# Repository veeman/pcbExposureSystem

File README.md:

# pcbExposureSystem
Homepage [www.mage-dev.de](http://www.mage-dev.de/)   
Copyright (c) 2012 Vitalij Mast <mailto:vitalij-mast(at)mage-dev(dot).de>  
License see LICENSE file

# Description
This is a pcb exposure system project.
This repo contains the schamtic files and the source code for the uC ATmega88.

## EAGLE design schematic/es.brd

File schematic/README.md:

Eagle Schematic Files   
# WARNING
High Voltages can cause electric shock. Be extremely careful when working with high voltage!   
Work with High Voltages at your own risk!

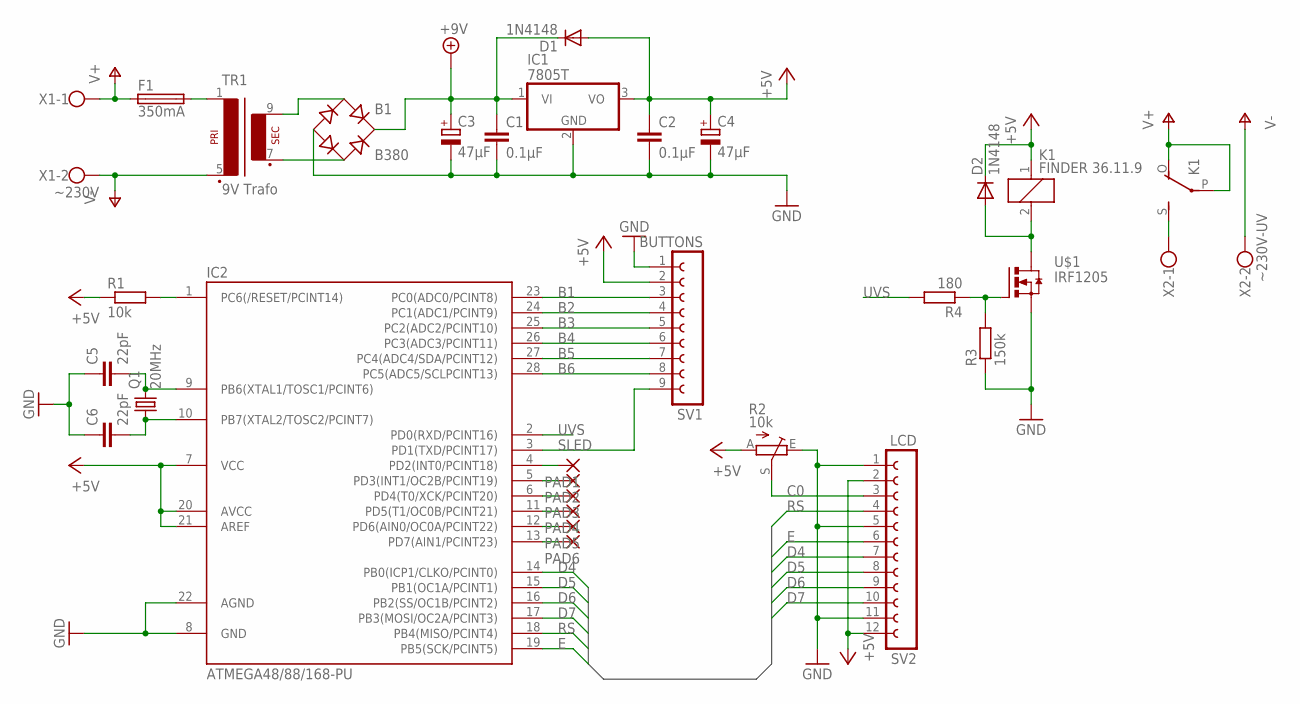
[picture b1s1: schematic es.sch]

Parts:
B1: B380; RB1A
C1, C2: 0.1µF; C025-024X044
C3, C4: 47µF; E2,5-5
C5, C6: 22pF; C050-024X044
D1, D2: 1N4148; DO35-7
F1: 350mA; SHK20Q
IC1: 7805T; TO220H
IC2: ATMEGA48/88/168-PU; DIL28-3
K1: FINDER 36.11.9; G5LE
PAD1, PAD2, PAD3, PAD4, PAD5, PAD6: 1,6/0,8
Q1: 20MHz; HC49/S
R1: 10k; 0204/7
R2: 10k; LI15
R3: 150k; 0204/7
R4: 180; 0204/7
SV1: BUTTONS; FE09
SV2: LCD; FE12
TR1: 9V Trafo; EI42-1
U$1: IRF1205; I-PAK_TO251AA
X1: ~230V; W237-2N
X2: ~230V-UV; W237-2N

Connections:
+5V: C2.1, C4.+, D1.A, D2.C, IC1.3 (VO), IC2.7 (VCC), IC2.20 (AVCC), IC2.21 (AREF), K1.1, R1.1, R2.A, SV1.2, SV2.2, SV2.12
+9V: B1.+, C1.1, C3.+, D1.C, IC1.1 (VI)
B1: IC2.23 (PC0(ADC0/PCINT8)), SV1.3
B2: IC2.24 (PC1(ADC1/PCINT9)), SV1.4
B3: IC2.25 (PC2(ADC2/PCINT10)), SV1.5
B4: IC2.26 (PC3(ADC3/PCINT11)), SV1.6
B5: IC2.27 (PC4(ADC4/SDA/PCINT12)), SV1.7
B6: IC2.28 (PC5(ADC5/SCLPCINT13)), SV1.8
C0: R2.S, SV2.3
D4: IC2.14 (PB0(ICP1/CLKO/PCINT0)), SV2.7
D5: IC2.15 (PB1(OC1A/PCINT1)), SV2.8
D6: IC2.16 (PB2(SS/OC1B/PCINT2)), SV2.9
D7: IC2.17 (PB3(MOSI/OC2A/PCINT3)), SV2.10
E: IC2.19 (PB5(SCK/PCINT5)), SV2.6
GND: B1.-, C1.2, C2.2, C3.-, C4.-, C5.1, C6.1, IC1.2 (GND), IC2.8 (GND), IC2.22 (AGND), R2.E, R3.1, SV1.1, SV2.1, SV2.5, SV2.11, U$1.3 (S)
unnamed: D2.A, K1.2, U$1.2 (D)
unnamed: IC2.4 (PD2(INT0/PCINT18)), PAD1.1
unnamed: C5.2, IC2.9 (PB6(XTAL1/TOSC1/PCINT6)), Q1.2
unnamed: B1.AC1, TR1.9 (S4)
unnamed: F1.2A (2), F1.2B, TR1.1
unnamed: K1.S, X2.1
unnamed: B1.AC2, TR1.7 (S3)
unnamed: IC2.5 (PD3(INT1/OC2B/PCINT19)), PAD2.1
unnamed: IC2.1 (PC6(/RESET/PCINT14)), R1.2
unnamed: C6.2, IC2.10 (PB7(XTAL2/TOSC2/PCINT7)), Q1.1
unnamed: IC2.6 (PD4(T0/XCK/PCINT20)), PAD3.1
unnamed: IC2.11 (PD5(T1/OC0B/PCINT21)), PAD4.1
unnamed: IC2.12 (PD6(AIN0/OC0A/PCINT22)), PAD5.1
unnamed: IC2.13 (PD7(AIN1/PCINT23)), PAD6.1
unnamed: R3.2, R4.1, U$1.1 (G)
RS: IC2.18 (PB4(MISO/PCINT4)), SV2.4
SLED: IC2.3 (PD1(TXD/PCINT17)), SV1.9
UVS: IC2.2 (PD0(RXD/PCINT16)), R4.2
V+: F1.1A (1), F1.1B, K1.O, K1.P, X1.1
V-: TR1.5 (P2), X1.2, X2.2

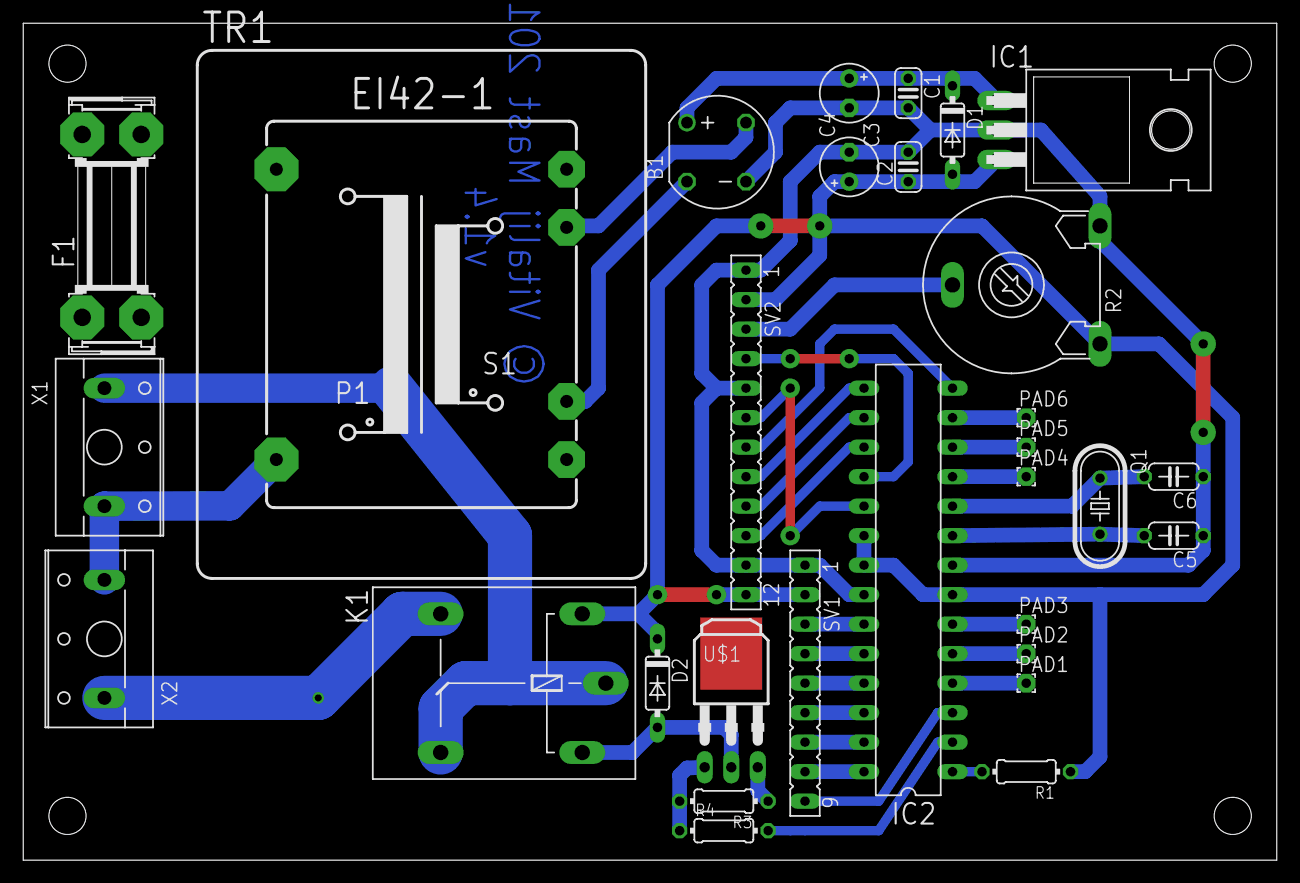
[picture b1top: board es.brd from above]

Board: 2 copper layers, 107.9 x 72.1 mm, 30 parts (0 on the bottom side), 35 nets.

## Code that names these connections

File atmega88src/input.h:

/**
 * Exposure System Project
 *
 * Copyright (c) 2009-2012 Vitalij Mast <vitalij-mast(at)mage-dev(dot).de>
 * All rights reserved.
 *
 */

#ifndef INPUT_H_INCLUDED
#define INPUT_H_INCLUDED

void input_init(void);

#define BUTTON_PORT     PINC
#define BUTTON_LEFT     PC2
#define BUTTON_RIGHT    PC4
#define BUTTON_UP       PC1
#define BUTTON_DOWN     PC5
#define BUTTON_OK       PC3
#define BUTTON_BACK     PC0

#define BTN_LEFT  !(BUTTON_PORT & (1 << BUTTON_LEFT))
#define BTN_RIGHT !(BUTTON_PORT & (1 << BUTTON_RIGHT))
#define BTN_UP    !(BUTTON_PORT & (1 << BUTTON_UP))
#define BTN_DOWN  !(BUTTON_PORT & (1 << BUTTON_DOWN))
#define BTN_OK    !(BUTTON_PORT & (1 << BUTTON_OK))
#define BTN_BACK  !(BUTTON_PORT & (1 << BUTTON_BACK))


#endif // INPUT_H_INCLUDED

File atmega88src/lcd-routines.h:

// Ansteuerung eines HD44780 kompatiblen LCD im 4-Bit-Interfacemodus
// http://www.mikrocontroller.net/articles/AVR-GCC-Tutorial/LCD-Ansteuerung
//
void lcd_data(unsigned char temp1);
void lcd_string(char *data, uint8_t InFlash);
void lcd_command(unsigned char temp1);
void lcd_enable(void);
void lcd_init(void);
void lcd_home(void);
void lcd_clear(void);
void lcd_clear_line(void);
void lcd_home(void);
void set_cursor(uint8_t x, uint8_t y);

// LCD Befehle

#define CLEAR_DISPLAY 0x01
#define CURSOR_HOME   0x02

// Pinbelegung für das LCD, an verwendete Pins anpassen

#define LCD_PORT      PORTB
#define LCD_DDR       DDRB
#define LCD_RS        PB4
#define LCD_EN        PB5
// DB4 bis DB7 des LCD sind mit PD0 bis PD3 des AVR verbunden

#define lcd_enable_cursor  lcd_command(0b00001111)
#define lcd_disable_cursor lcd_command(0b00001100)

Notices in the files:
schematic/es.brd:
© Vitalij Mast 2010
